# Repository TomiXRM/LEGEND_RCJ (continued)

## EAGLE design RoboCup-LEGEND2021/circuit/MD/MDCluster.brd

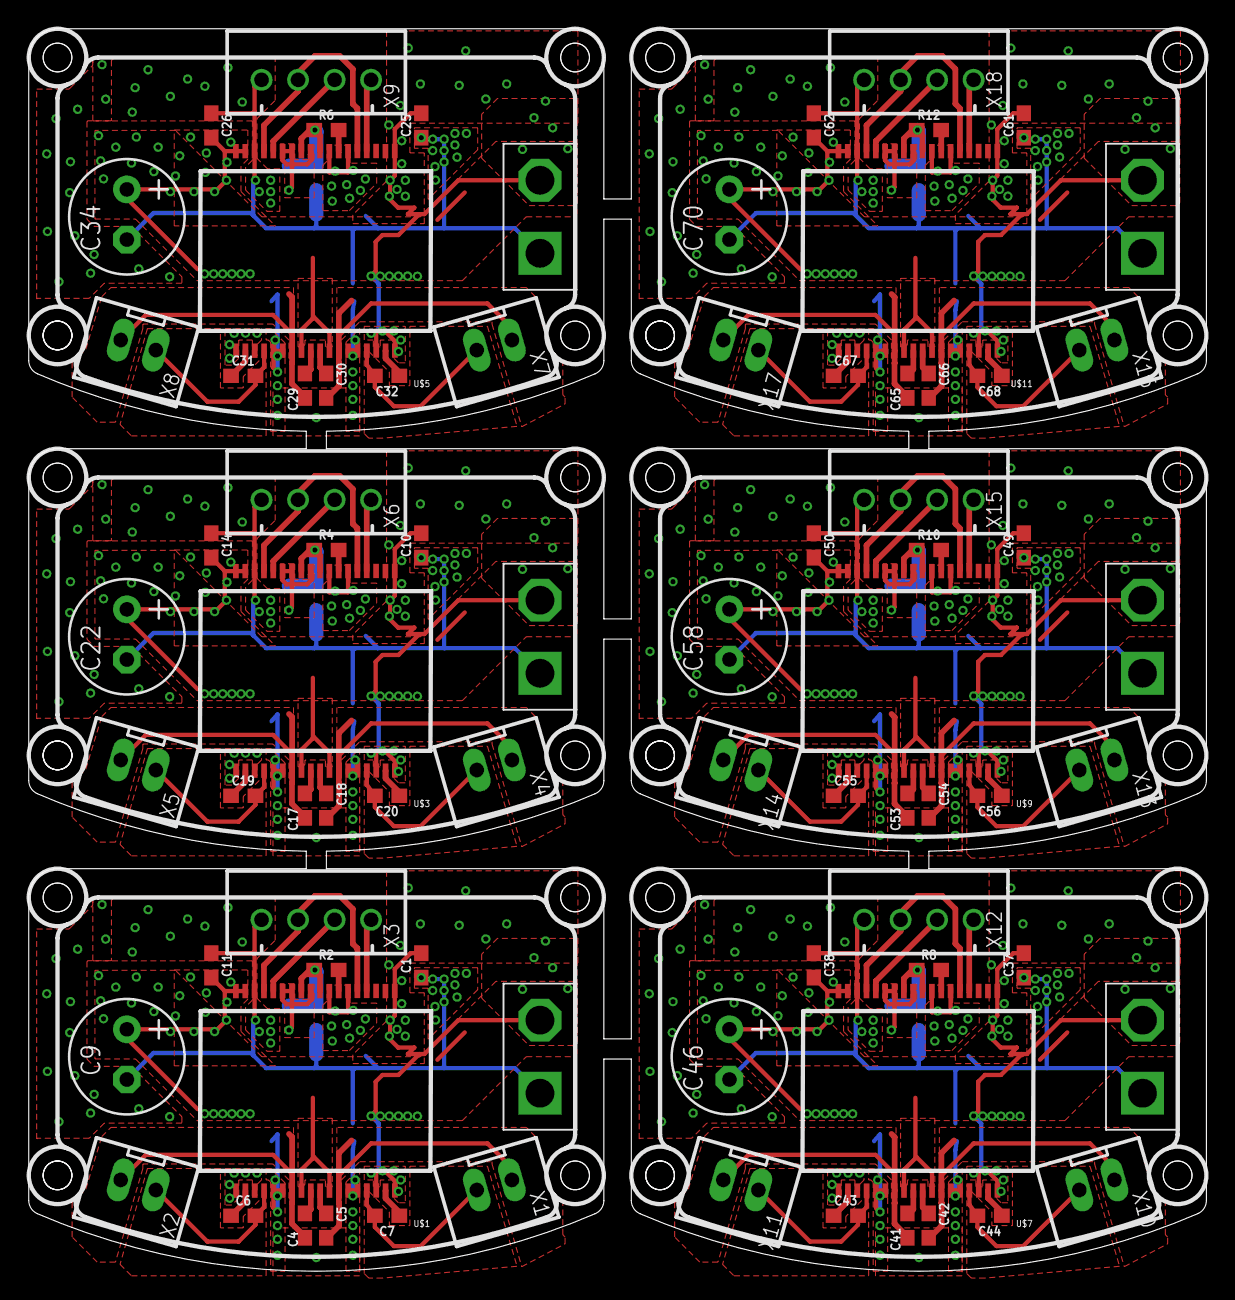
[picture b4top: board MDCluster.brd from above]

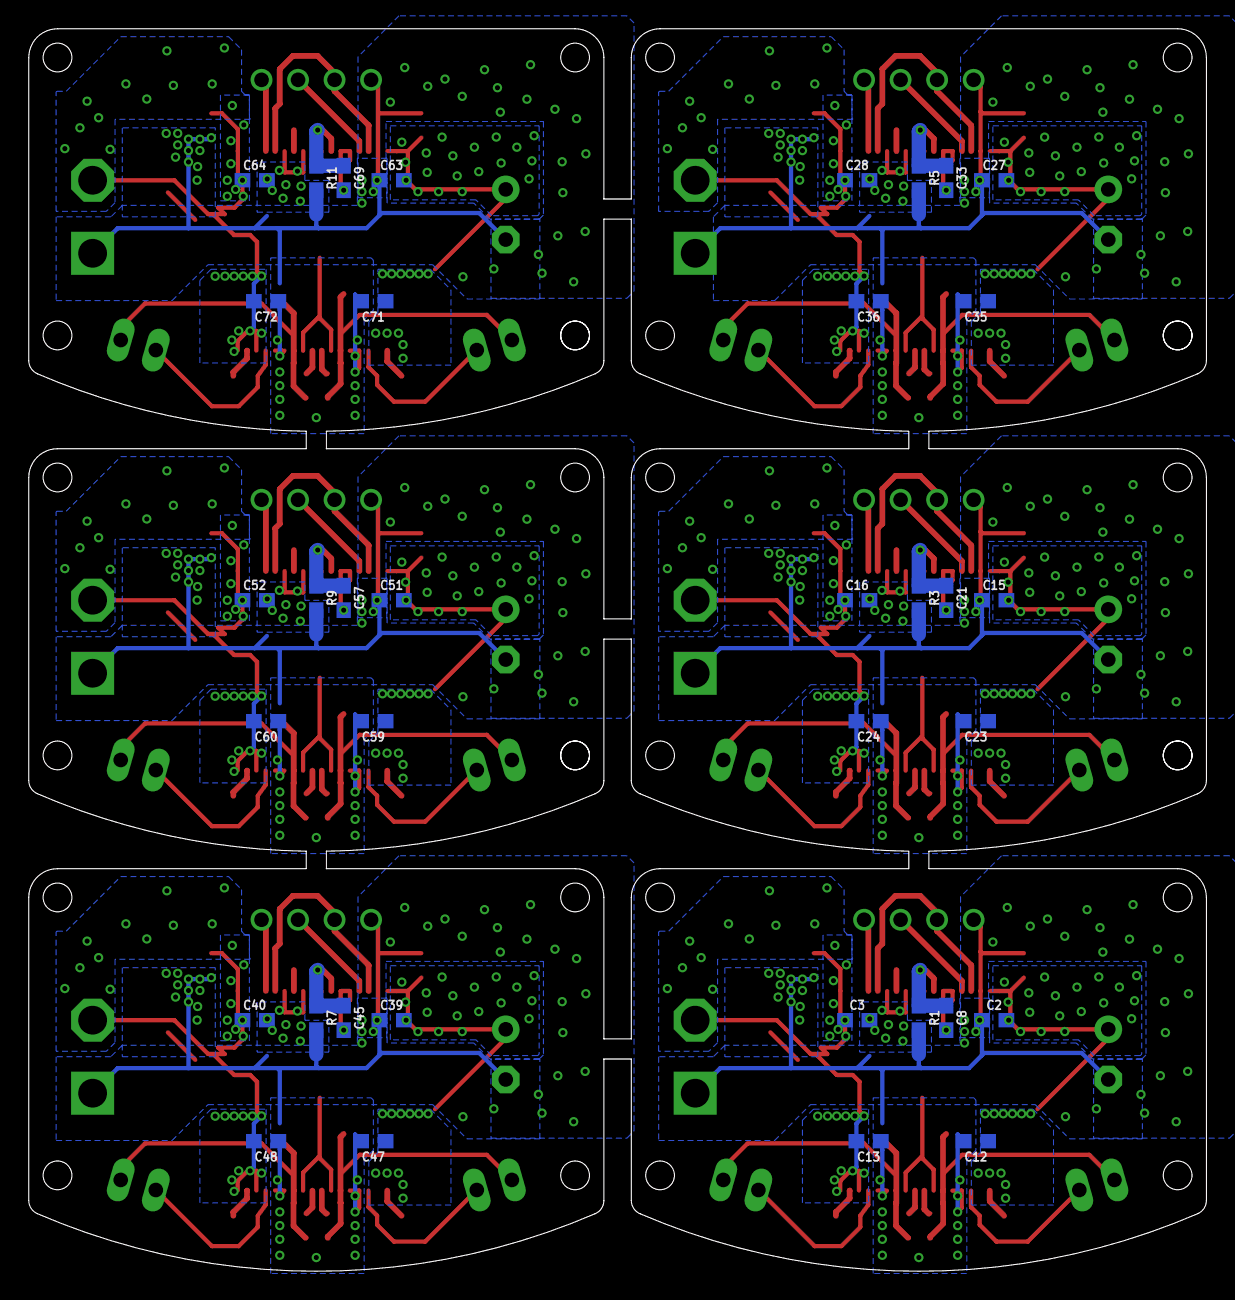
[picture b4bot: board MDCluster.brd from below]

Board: 2 copper layers, 81.9 x 86.4 mm, 114 parts (36 on the bottom side), 96 nets.

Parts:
C1, C2, C3, C4, C5, C6, C7, C8, C10, C11, C12, C13, C14, C15, C16, C17, C18, C19, C20, C21, C23, C24, C25, C26, C27, C28, C29, C30, C31, C32, C33, C35, C36, C37, C38, C39, C40, C41, C42, C43, C44, C45, C47, C48, C49, C50, C51, C52, C53, C54, C55, C56, C57, C59, C60, C61, C62, C63, C64, C65, C66, C67, C68, C69, C71, C72: 0.1uF; 0603
C9, C22, C34, C46, C58, C70: E3,5-8
R1, R3, R5, R7, R9, R11: 1; 0603
R2, R4, R6, R8, R10, R12: 47k; 0603
U$1, U$3, U$5, U$7, U$9, U$11: DRV8432DKDR; HSSOP-36
U$2, U$4, U$6, U$8, U$10, U$12: BAT
X1, X2, X4, X5, X7, X8, X10, X11, X13, X14, X16, X17: JST-XH-02-PIN-LONG-PAD; JST-XH-02-PACKAGE-LONG-PAD
X3, X6, X9, X12, X15, X18: JST-XH-04-PIN-ROUND-PAD; JST-XH-04-PACKAGE-ROUND-PAD

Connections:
AGND1: C8.1, R1.1, R2.1, U$1.AGND, U$1.M3
AGND2: C21.1, R3.1, R4.1, U$3.AGND, U$3.M3
AGND3: C33.1, R5.1, R6.1, U$5.AGND, U$5.M3
AGND4: C45.1, R7.1, R8.1, U$7.AGND, U$7.M3
AGND5: C57.1, R9.1, R10.1, U$9.AGND, U$9.M3
AGND6: C69.1, R11.1, R12.1, U$11.AGND, U$11.M3
GND: C1.1, C2.1, C3.2, C9.-, C11.1, C12.2, C13.1, R1.2, U$1.GND, U$1.GND_A, U$1.GND_B, U$1.GND_C, U$1.GND_D, U$1.PWM_B, U$1.PWM_D, U$2.G, X3.1
GND1: C10.1, C14.1, C15.1, C16.2, C22.-, C23.2, C24.1, R3.2, U$3.GND, U$3.GND_A, U$3.GND_B, U$3.GND_C, U$3.GND_D, U$3.PWM_B, U$3.PWM_D, U$4.G, X6.1
GND2: C25.1, C26.1, C27.1, C28.2, C34.-, C35.2, C36.1, R5.2, U$5.GND, U$5.GND_A, U$5.GND_B, U$5.GND_C, U$5.GND_D, U$5.PWM_B, U$5.PWM_D, U$6.G, X9.1
GND3: C37.1, C38.1, C39.1, C40.2, C46.-, C47.2, C48.1, R7.2, U$7.GND, U$7.GND_A, U$7.GND_B, U$7.GND_C, U$7.GND_D, U$7.PWM_B, U$7.PWM_D, U$8.G, X12.1
GND4: C49.1, C50.1, C51.1, C52.2, C58.-, C59.2, C60.1, R9.2, U$9.GND, U$9.GND_A, U$9.GND_B, U$9.GND_C, U$9.GND_D, U$9.PWM_B, U$9.PWM_D, U$10.G, X15.1
GND5: C61.1, C62.1, C63.1, C64.2, C70.-, C71.2, C72.1, R11.2, U$11.GND, U$11.GND_A, U$11.GND_B, U$11.GND_C, U$11.GND_D, U$11.PWM_B, U$11.PWM_D, U$12.G, X18.1
M1_1: C7.2, U$1.OUT_A, X1.2
M1_2: C5.2, U$1.OUT_B, X1.1
M1_3: C18.2, U$3.OUT_B, X4.1
M1_4: C20.2, U$3.OUT_A, X4.2
M1_5: C30.2, U$5.OUT_B, X7.1
M1_6: C32.2, U$5.OUT_A, X7.2
M1_7: C42.2, U$7.OUT_B, X10.1
M1_8: C44.2, U$7.OUT_A, X10.2
M1_9: C54.2, U$9.OUT_B, X13.1
M1_10: C56.2, U$9.OUT_A, X13.2
M1_11: C66.2, U$11.OUT_B, X16.1
M1_12: C68.2, U$11.OUT_A, X16.2
M2_1: C4.2, U$1.OUT_C, X2.2
M2_2: C6.2, U$1.OUT_D, X2.1
M2_3: C19.2, U$3.OUT_D, X5.1
M2_4: C17.2, U$3.OUT_C, X5.2
M2_5: C31.2, U$5.OUT_D, X8.1
M2_6: C29.2, U$5.OUT_C, X8.2
M2_7: C43.2, U$7.OUT_D, X11.1
M2_8: C41.2, U$7.OUT_C, X11.2
M2_9: C55.2, U$9.OUT_D, X14.1
M2_10: C53.2, U$9.OUT_C, X14.2
M2_11: C67.2, U$11.OUT_D, X17.1
M2_12: C65.2, U$11.OUT_C, X17.2
MDRST: U$1.RESET_AB, U$1.RESET_CD, X3.2
MDRST1: U$3.RESET_AB, U$3.RESET_CD, X6.2
MDRST2: U$5.RESET_AB, U$5.RESET_CD, X9.2
MDRST3: U$7.RESET_AB, U$7.RESET_CD, X12.2
MDRST4: U$9.RESET_AB, U$9.RESET_CD, X15.2
MDRST5: U$11.RESET_AB, U$11.RESET_CD, X18.2
unnamed: C19.1, U$3.BST_D
unnamed: C17.1, U$3.BST_C
unnamed: C18.1, U$3.BST_B
unnamed: C20.1, U$3.BST_A
unnamed: C6.1, U$1.BST_D
unnamed: C4.1, U$1.BST_C
unnamed: C5.1, U$1.BST_B
unnamed: C7.1, U$1.BST_A
unnamed: R4.2, U$3.OC_ADJ
unnamed: C31.1, U$5.BST_D
unnamed: C29.1, U$5.BST_C
unnamed: R2.2, U$1.OC_ADJ
unnamed: C30.1, U$5.BST_B
unnamed: C32.1, U$5.BST_A
unnamed: R6.2, U$5.OC_ADJ
unnamed: C43.1, U$7.BST_D
unnamed: C41.1, U$7.BST_C
unnamed: C42.1, U$7.BST_B
unnamed: C44.1, U$7.BST_A
unnamed: R8.2, U$7.OC_ADJ
unnamed: C55.1, U$9.BST_D
unnamed: C53.1, U$9.BST_C
unnamed: C54.1, U$9.BST_B
unnamed: C56.1, U$9.BST_A
unnamed: R10.2, U$9.OC_ADJ
unnamed: C67.1, U$11.BST_D
unnamed: C65.1, U$11.BST_C
unnamed: C66.1, U$11.BST_B
unnamed: C68.1, U$11.BST_A
unnamed: R12.2, U$11.OC_ADJ
PWM1: U$1.PWM_A, X3.4
PWM2: U$1.PWM_C, X3.3
PWM3: U$3.PWM_C, X6.3
PWM4: U$3.PWM_A, X6.4
PWM5: U$5.PWM_C, X9.3
PWM6: U$5.PWM_A, X9.4
PWM7: U$7.PWM_C, X12.3
PWM8: U$7.PWM_A, X12.4
PWM9: U$9.PWM_C, X15.3
PWM10: U$9.PWM_A, X15.4
PWM11: U$11.PWM_C, X18.3
PWM12: U$11.PWM_A, X18.4
VM: C1.2, C2.2, C3.1, C9.+, C11.2, C12.1, C13.2, U$1.GVDD_A, U$1.GVDD_B, U$1.GVDD_C, U$1.GVDD_D, U$1.PVDD_A, U$1.PVDD_B, U$1.PVDD_C, U$1.PVDD_D, U$1.VDD, U$2.+
VM1: C10.2, C14.2, C15.2, C16.1, C22.+, C23.1, C24.2, U$3.GVDD_A, U$3.GVDD_B, U$3.GVDD_C, U$3.GVDD_D, U$3.PVDD_A, U$3.PVDD_B, U$3.PVDD_C, U$3.PVDD_D, U$3.VDD, U$4.+
VM2: C25.2, C26.2, C27.2, C28.1, C34.+, C35.1, C36.2, U$5.GVDD_A, U$5.GVDD_B, U$5.GVDD_C, U$5.GVDD_D, U$5.PVDD_A, U$5.PVDD_B, U$5.PVDD_C, U$5.PVDD_D, U$5.VDD, U$6.+
VM3: C37.2, C38.2, C39.2, C40.1, C46.+, C47.1, C48.2, U$7.GVDD_A, U$7.GVDD_B, U$7.GVDD_C, U$7.GVDD_D, U$7.PVDD_A, U$7.PVDD_B, U$7.PVDD_C, U$7.PVDD_D, U$7.VDD, U$8.+
VM4: C49.2, C50.2, C51.2, C52.1, C58.+, C59.1, C60.2, U$9.GVDD_A, U$9.GVDD_B, U$9.GVDD_C, U$9.GVDD_D, U$9.PVDD_A, U$9.PVDD_B, U$9.PVDD_C, U$9.PVDD_D, U$9.VDD, U$10.+
VM5: C61.2, C62.2, C63.2, C64.1, C70.+, C71.1, C72.2, U$11.GVDD_A, U$11.GVDD_B, U$11.GVDD_C, U$11.GVDD_D, U$11.PVDD_A, U$11.PVDD_B, U$11.PVDD_C, U$11.PVDD_D, U$11.VDD, U$12.+
VREG1: C8.2, U$1.M1, U$1.M2, U$1.VREG
VREG2: C21.2, U$3.M1, U$3.M2, U$3.VREG
VREG3: C33.2, U$5.M1, U$5.M2, U$5.VREG
VREG4: C45.2, U$7.M1, U$7.M2, U$7.VREG
VREG5: C57.2, U$9.M1, U$9.M2, U$9.VREG
VREG6: C69.2, U$11.M1, U$11.M2, U$11.VREG

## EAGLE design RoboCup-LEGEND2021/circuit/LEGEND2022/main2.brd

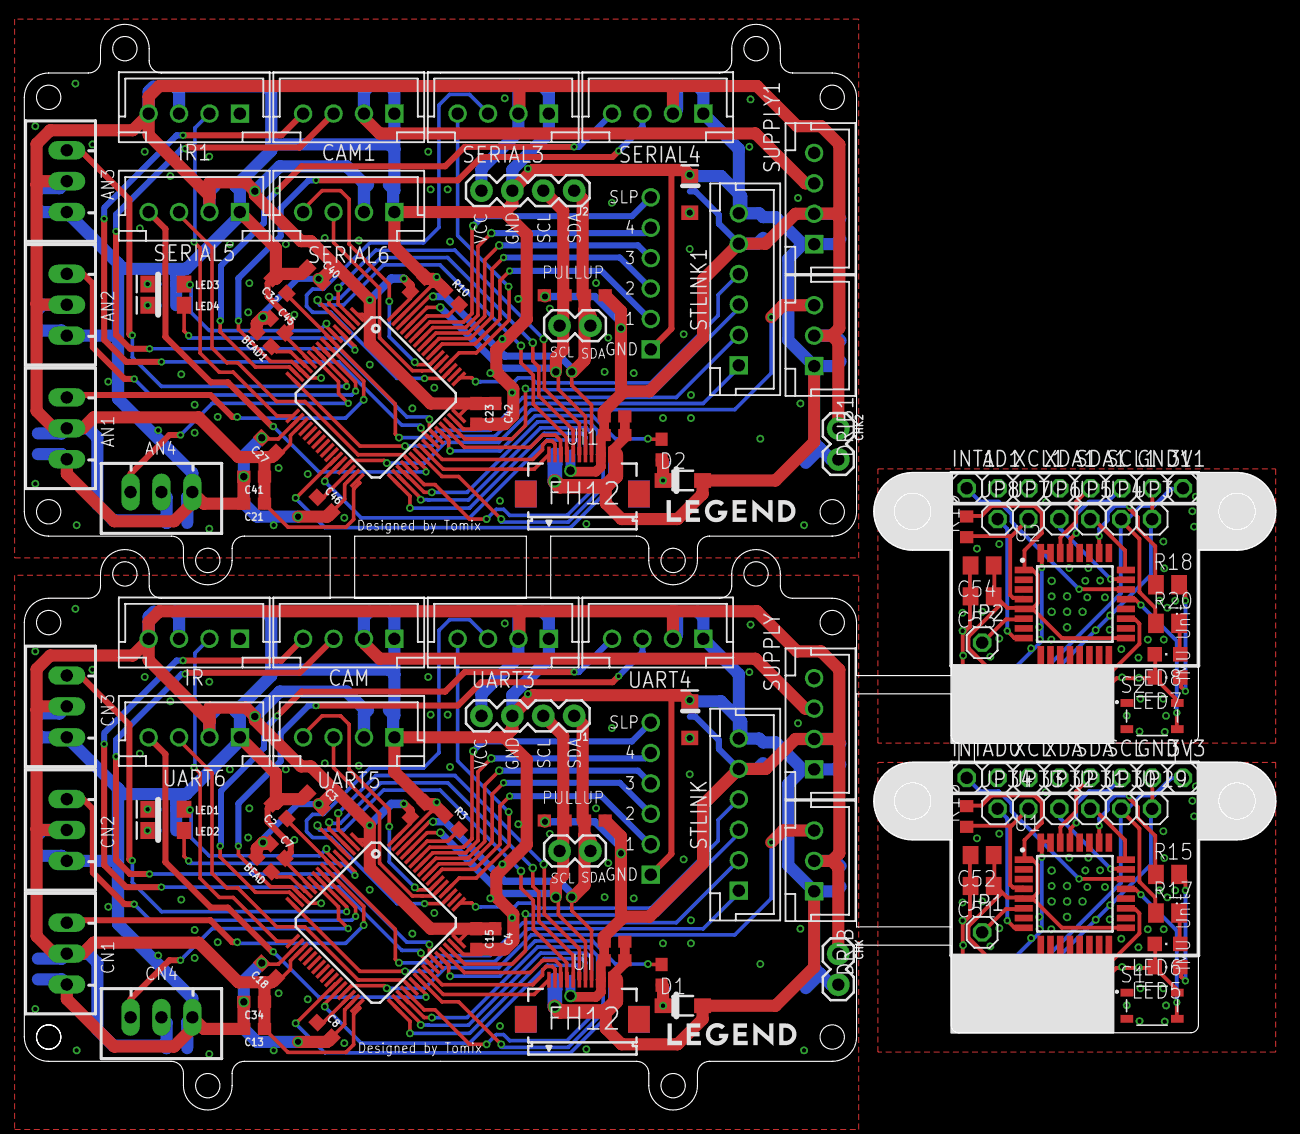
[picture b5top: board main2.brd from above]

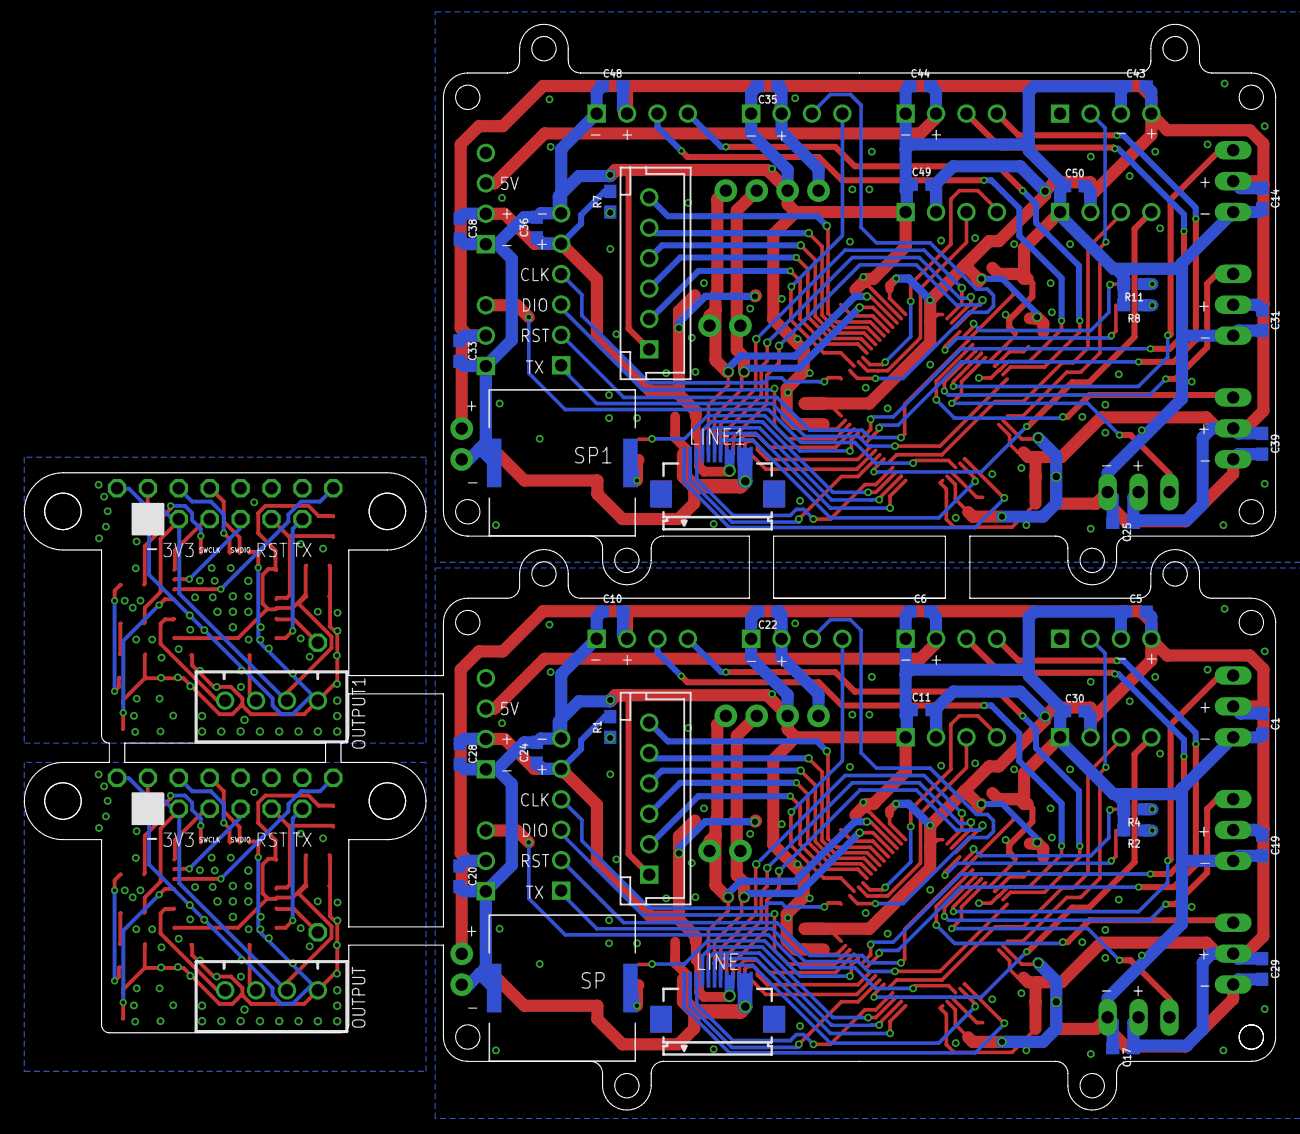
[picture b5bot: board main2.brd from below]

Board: 2 copper layers, 102.9 x 89.3 mm, 166 parts (40 on the bottom side), 136 nets.

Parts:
3V1, 3V3: 1X01
AD0, AD1: 1X01
AN1: 1; JST-XH-03-PACKAGE-LONG-PAD
AN2: 2; JST-XH-03-PACKAGE-LONG-PAD
AN3: 3; JST-XH-03-PACKAGE-LONG-PAD
AN4: 4; JST-XH-03-PACKAGE-LONG-PAD
BEAD, BEAD1: 0; 0603
C1, C14: 0.1uF; 1608
C2, C3, C4, C5, C6, C7, C10, C11, C12, C13, C15, C16, C17, C18, C19, C20, C21, C22, C23, C24, C25, C27, C30, C31, C32, C33, C35, C36, C40, C42, C43, C44, C45, C48, C49, C50: 0.1UF_1608; 1608
C8, C46: 4.7uF; 0603
C9, C34, C41, C47: 0.1uF; 0603
C26, C37: 0.001UF_1608; 1608
C28, C29, C38, C39: 1.0UF_1608; 1608
C51, C52, C53, C54: 0.1u; C0805
CAM, CAM1: cam; B4B-XH-A
CHK, CHK1, CHK2, CHK3: +3V3; 1X02
CN1: 1; JST-XH-03-PACKAGE-LONG-PAD
CN2: 2; JST-XH-03-PACKAGE-LONG-PAD
CN3: 3; JST-XH-03-PACKAGE-LONG-PAD
CN4: 4; JST-XH-03-PACKAGE-LONG-PAD
D1, D2: DIODE-SS2040LFL; SOD123FL
DRIB, DRIB1: B3B-XH-A
GND, GND1: 1X01
INT, INT1: 1X01
IR, IR1: IR; B4B-XH-A
J1, J2: 1X04
JP1, JP2, JP3, JP4, JP5, JP6, JP7, JP8, JP29, JP30, JP31, JP32, JP33, JP34: 1X01
LED1, LED2, LED3, LED4: LED-1206
LED5, LED6, LED7, LED8: CHIPLED_0805
LINE, LINE1: FH12-12S-0.5SH
MD_A, MD_A1: B6B-XH-A
NUCLEO_MAIN, NUCLEO_MAIN1: F446RET6; STM32F446RET6
OUTPUT, OUTPUT1: JST-XH-04-PIN-ROUND-PAD; JST-XH-04-PACKAGE-ROUND-PAD
PILOT, PILOT1: LED-1206
R1, R2, R4, R5, R6, R7, R8, R9, R11, R12, R13, R14: 1k; R0603
R3, R10, R16, R19: 10k; R0603
R15, R17, R18, R20: 1k; M0805
S1, S2: SKRPACE010; SW_SKRPACE010
SCL, SCL1: 1X01
SDA, SDA1: 1X01
SERIAL3, SERIAL4, SERIAL5, SERIAL6: IMU; B4B-XH-A
SP, SP1: PKLCS1212E4001
STLINK, STLINK1: MAIN; B6B-XH-A
SUPPLY, SUPPLY1: B4B-XH-A
U1, U2: STM32F303K8T6; QFP80P900X900X160-32N
UART3, UART4, UART5, UART6: IMU; B4B-XH-A
UI, UI1: FH12-12S-0.5SH
XCL, XCL1: 1X01
XDA, XDA1: 1X01

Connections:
+3V1: 3V1.1, C53.1, C54.1, JP4.1, OUTPUT1.2, R19.2, R20.1, U2.1, U2.5, U2.17
+3V3: 3V3.1, C51.1, C52.1, JP30.1, OUTPUT.2, R16.2, R17.1, U1.1, U1.5, U1.17
+5V: C6.2, CAM.2, SUPPLY.3
+5V1: C44.2, CAM1.2, SUPPLY1.3
A0: JP1.1, U1.6
A9: JP2.1, U2.6
ANALOG: OUTPUT.3, U1.10
ANALOG1: OUTPUT1.3, U2.10
BALLRX: IR.2, NUCLEO_MAIN.PA3
BALLRX1: IR1.2, NUCLEO_MAIN1.PA3
BOOT0: NUCLEO_MAIN.BOOT0, R3.2
BOOT1: NUCLEO_MAIN1.BOOT0, R10.2
BUTTON_CENTER: NUCLEO_MAIN.PC14, UI.5
BUTTON_CENTER1: NUCLEO_MAIN1.PC14, UI1.5
BUTTON_LEFT: NUCLEO_MAIN.PC15, UI.4
BUTTON_LEFT1: NUCLEO_MAIN1.PC15, UI1.4
BUTTON_RIGHT: NUCLEO_MAIN.PC13, UI.6
BUTTON_RIGHT1: NUCLEO_MAIN1.PC13, UI1.6
BUZZER: NUCLEO_MAIN.PA11, R9.1
BUZZER1: NUCLEO_MAIN1.PA11, R12.1
CN1: CN1.3, NUCLEO_MAIN.PC0
CN2: CN2.3, NUCLEO_MAIN.PC1
CN3: CN3.3, NUCLEO_MAIN.PC2
CN4: CN4.3, NUCLEO_MAIN.PC3
CN5: AN1.3, NUCLEO_MAIN1.PC0
CN6: AN2.3, NUCLEO_MAIN1.PC1
CN7: AN3.3, NUCLEO_MAIN1.PC2
CN8: AN4.3, NUCLEO_MAIN1.PC3
D5: R18.1, U2.26
D13: R15.1, U1.26
DRIB_PWM: DRIB.3, NUCLEO_MAIN.PB10
DRIB_PWM1: DRIB1.3, NUCLEO_MAIN1.PB10
GND: C51.2, C52.2, GND.1, JP29.1, LED5.C, LED6.C, OUTPUT.1, S1.2, U1.16, U1.31, U1.32
GND1: C53.2, C54.2, GND1.1, JP3.1, LED7.C, LED8.C, OUTPUT1.1, S2.2, U2.16, U2.31, U2.32
INT: INT.1, U1.22
INT1: INT1.1, U2.22
LED1: LED1.A, NUCLEO_MAIN.PH1
LED2: LED2.A, NUCLEO_MAIN.PH0
LED3: LED4.A, NUCLEO_MAIN1.PH0
LED4: LED3.A, NUCLEO_MAIN1.PH1
LINE_A0: LINE.6, NUCLEO_MAIN.PB12
LINE_A1: LINE.5, NUCLEO_MAIN.PB13
LINE_A2: LINE.4, NUCLEO_MAIN.PB14
LINE_A3: LINE.3, NUCLEO_MAIN.PB15
LINE_A4: LINE.2, NUCLEO_MAIN.PC8
LINE_A5: LINE1.2, NUCLEO_MAIN1.PC8
LINE_A6: LINE1.3, NUCLEO_MAIN1.PB15
LINE_A7: LINE1.4, NUCLEO_MAIN1.PB14
LINE_A8: LINE1.5, NUCLEO_MAIN1.PB13
LINE_A9: LINE1.6, NUCLEO_MAIN1.PB12
LINE_ANALOG: LINE.1, NUCLEO_MAIN.PB1
LINE_ANALOG1: LINE1.1, NUCLEO_MAIN1.PB1
LINE_PWM: LINE.7, NUCLEO_MAIN.PB2
LINE_PWM1: LINE1.7, NUCLEO_MAIN1.PB2
unnamed: LED2.C, R2.1
unnamed: LED1.C, R4.1
unnamed: LED4.C, R8.1
unnamed: LED3.C, R11.1
unnamed: LED5.A, R15.2
unnamed: LED6.A, R17.2
unnamed: LED7.A, R18.2
unnamed: LED8.A, R20.2
NRST: C2.1, NUCLEO_MAIN.NRST, STLINK.2
NRST1: C32.1, NUCLEO_MAIN1.NRST, STLINK1.2
PH1: MD_A.2, NUCLEO_MAIN.PB3
PH2: MD_A.3, NUCLEO_MAIN.PB4
PH3: MD_A.4, NUCLEO_MAIN.PB5
PH4: MD_A.5, NUCLEO_MAIN.PB6
PH5: MD_A1.4, NUCLEO_MAIN1.PB5
PH6: MD_A1.3, NUCLEO_MAIN1.PB4
PH7: MD_A1.2, NUCLEO_MAIN1.PB3
PH8: MD_A1.5, NUCLEO_MAIN1.PB6
POWERLED_RESISTOR: PILOT.A, R1.1
POWERLED_RESISTOR1: PILOT1.A, R7.1
RESET: JP33.1, R16.1, U1.4
RESET1: JP7.1, R19.1, U2.4
RGB_B: NUCLEO_MAIN.PA12, UI.3
RGB_B1: NUCLEO_MAIN1.PA12, UI1.3
RGB_G: NUCLEO_MAIN.PA8, UI.2
RGB_G1: NUCLEO_MAIN1.PA8, UI1.2
RGB_R: NUCLEO_MAIN.PC9, UI.1
RGB_R1: NUCLEO_MAIN1.PC9, UI1.1
SCL: CHK1.1, J1.2, NUCLEO_MAIN.PB8, R6.1, UI.7
SCL1: CHK3.1, J2.2, NUCLEO_MAIN1.PB8, R14.1, UI1.7
SCL2: SCL.1, U1.29
SCL3: SCL1.1, U2.29
SDA: CHK1.2, J1.1, NUCLEO_MAIN.PB9, R5.1, UI.8
SDA1: CHK3.2, J2.1, NUCLEO_MAIN1.PB9, R13.1, UI1.8
SDA2: SDA.1, U1.30
SDA3: SDA1.1, U2.30
SERIAL1RX: CAM.3, NUCLEO_MAIN.PA10
SERIAL1RX1: CAM1.3, NUCLEO_MAIN1.PA10
SERIAL1TX: CAM.4, NUCLEO_MAIN.PA9
SERIAL1TX1: CAM1.4, NUCLEO_MAIN1.PA9
SERIAL3RX: NUCLEO_MAIN.PC11, UART3.4
SERIAL3RX1: NUCLEO_MAIN1.PC11, SERIAL3.4
SERIAL3TX: NUCLEO_MAIN.PC10, UART3.3
SERIAL3TX1: NUCLEO_MAIN1.PC10, SERIAL3.3
SERIAL4RX: NUCLEO_MAIN.PA1, UART4.4
SERIAL4RX1: NUCLEO_MAIN1.PA1, SERIAL4.4
SERIAL4TX: NUCLEO_MAIN.PA0, UART4.3
SERIAL4TX1: NUCLEO_MAIN1.PA0, SERIAL4.3
SERIAL5RX: NUCLEO_MAIN.PD2, UART5.4
SERIAL5RX1: NUCLEO_MAIN1.PD2, SERIAL6.4
SERIAL5TX: NUCLEO_MAIN.PC12, UART5.3
SERIAL5TX1: NUCLEO_MAIN1.PC12, SERIAL6.3
SERIAL6RX: NUCLEO_MAIN.PC7, UART6.4
SERIAL6RX1: NUCLEO_MAIN1.PC7, SERIAL5.4
SERIAL6TX: NUCLEO_MAIN.PC6, UART6.3
SERIAL6TX1: NUCLEO_MAIN1.PC6, SERIAL5.3
SLEEP: MD_A.6, NUCLEO_MAIN.PB7
SLEEP1: MD_A1.6, NUCLEO_MAIN1.PB7
SP: D1.C, R9.2, SP.1
SP1: D2.C, R12.2, SP1.1
SW: S1.4, U1.21
SW1: S2.4, U2.21
SWCLK: NUCLEO_MAIN.PA14, STLINK.4
SWCLK1: NUCLEO_MAIN1.PA14, STLINK1.4
SWCLK2: JP31.1, U1.24
SWCLK3: JP5.1, U2.24
SWDIO: NUCLEO_MAIN.PA13, STLINK.3
SWDIO1: NUCLEO_MAIN1.PA13, STLINK1.3
SWDIO2: JP32.1, U1.23
SWDIO3: JP6.1, U2.23
TX1: OUTPUT.4, U1.19
TX2: OUTPUT1.4, U2.19
USBTX: NUCLEO_MAIN.PA2, STLINK.1
USBTX1: NUCLEO_MAIN1.PA2, STLINK1.1
USBTX2: JP34.1, U1.8
USBTX3: JP8.1, U2.8
VCAP: C8.1, NUCLEO_MAIN.VCAP_1
VCAP1: C46.1, NUCLEO_MAIN1.VCAP_1
VCC: AN1.2, AN2.2, AN3.2, AN4.2, BEAD.2, BEAD1.2, C1.1, C3.2, C4.1, C5.2, C7.1, C9.1, C10.2, C11.2, C12.1, C13.1, C14.1, C15.1, C16.1, C17.1, C18.1, C19.1, C20.1, C21.1, C22.1, C23.1, C24.1, C25.1, C26.1, C27.1, C28.1, C29.1, C30.2, C31.1, C33.1, C34.1, C35.1, C36.1, C37.1, C38.1, C39.1, C40.2, C41.1, C42.1, C43.2, C45.1, C47.1, C48.2, C49.2, C50.2, CHK.1, CHK2.1, CN1.2, CN2.2, CN3.2, CN4.2, DRIB.2, DRIB1.2, IR.4, IR1.4, J1.4, J2.4, LINE.8, LINE.9, LINE1.8, LINE1.9, NUCLEO_MAIN.VBAT, NUCLEO_MAIN.VDD, NUCLEO_MAIN.VDD1, NUCLEO_MAIN.VDD2, NUCLEO_MAIN.VDD3, NUCLEO_MAIN1.VBAT, NUCLEO_MAIN1.VDD, NUCLEO_MAIN1.VDD1, NUCLEO_MAIN1.VDD2, NUCLEO_MAIN1.VDD3, R1.2, R5.2, R6.2, R7.2, R13.2, R14.2, SERIAL3.2, SERIAL4.2, SERIAL5.2, SERIAL6.2, STLINK.5, STLINK1.5, SUPPLY.2, SUPPLY1.2, UART3.2, UART4.2, UART5.2, UART6.2, UI.9, UI.10, UI1.9, UI1.10
VDDA: BEAD.1, NUCLEO_MAIN.VREF+
VDDA1: BEAD1.1, NUCLEO_MAIN1.VREF+
VSS: AN1.1, AN2.1, AN3.1, AN4.1, C1.2, C2.2, C3.1, C4.2, C5.1, C6.1, C7.2, C8.2, C9.2, C10.1, C11.1, C12.2, C13.2, C14.2, C15.2, C16.2, C17.2, C18.2, C19.2, C20.2, C21.2, C22.2, C23.2, C24.2, C25.2, C26.2, C27.2, C28.2, C29.2, C30.1, C31.2, C32.2, C33.2, C34.2, C35.2, C36.2, C37.2, C38.2, C39.2, C40.1, C41.2, C42.2, C43.1, C44.1, C45.2, C46.2, C47.2, C48.1, C49.1, C50.1, CAM.1, CAM1.1, CHK.2, CHK2.2, CN1.1, CN2.1, CN3.1, CN4.1, D1.A, D2.A, DRIB.1, DRIB1.1, IR.3, IR1.3, J1.3, J2.3, LINE.10, LINE.11, LINE.12, LINE1.10, LINE1.11, LINE1.12, MD_A.1, MD_A1.1, NUCLEO_MAIN.VREF-, NUCLEO_MAIN.VSS, NUCLEO_MAIN.VSS1, NUCLEO_MAIN.VSS2, NUCLEO_MAIN.VSS3, NUCLEO_MAIN1.VREF-, NUCLEO_MAIN1.VSS, NUCLEO_MAIN1.VSS1, NUCLEO_MAIN1.VSS2, NUCLEO_MAIN1.VSS3, PILOT.C, PILOT1.C, R2.2, R3.1, R4.2, R8.2, R10.1, R11.2, SERIAL3.1, SERIAL4.1, SERIAL5.1, SERIAL6.1, SP.2, SP1.2, STLINK.6, STLINK1.6, SUPPLY.1, SUPPLY1.1, UART3.1, UART4.1, UART5.1, UART6.1, UI.11, UI.12, UI1.11, UI1.12

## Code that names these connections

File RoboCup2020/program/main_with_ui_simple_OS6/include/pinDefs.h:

#pragma once
//LED
#define LED1 PB_8
#define LED2 PB_9
#define LED3 PF_13

//LINE Sensor
#define LINE_SIG PA_0
#define LINE_A0 PG_2
#define LINE_A1 PG_3
#define LINE_A2 PG_4
#define LINE_A3 PG_5
#define LINE_A4 PG_6
#define LINE_PWM PD_15

//Button
#define BUTTON_LEFT PD_7
#define BUTTON_CENTRE PG_9
#define BUTTON_RIGHT PG_10

//Buzzer
#define BUZZER PC_6

//Dribbler
#define DRIB_PWM PE_5

//Kicker
#define KICKER_PHOTO1 PA_2
#define KICKER_PHOTO2 PA_3
#define KICKER_KICK PF_2

//EEPROM
#define EEPROM_SDA PF_0
#define EEPROM_SCL PF_1

//INA219
#define INA219_SDA PC_9
#define INA219_SCL PA_8

//OLED
#define LCD_SDA PB_7
#define LCD_SCL PB_6

//I2C (FREE)
#define I2C_SDA PF_15
#define I2C_SCL PF_14

//CN (ADC)
#define CN1 PF_3
#define CN2 PF_4
#define CN3 PF_5
#define CN4 PF_6
#define CN5 PF_7
#define CN6 PF_8
#define CN7 PF_9
#define CN8 PF_10
#define CN9 PC_0
#define CN10 PC_1
#define CN11 PC_2

//Bridge
#define BRIDGE_TX PA_9
#define BRIDGE_RX PA_10
#define BRIDGE_IO1 PA_4
#define BRIDGE_IO2 PA_5

//UART
#define UART_A_TX PG_14
#define UART_A_RX PC_7

#define UART_B_TX PE_8
#define UART_B_RX PE_7

#define UART_C_TX PE_1
#define UART_C_RX PE_0

//IMU
#define IMU_TX PC_10
#define IMU_RX PC_11

//MOUSE
#define MOUSE_TX PC_12
#define MOUSE_RX PD_2

//CAM
#define CAM_TX PD_5
#define CAM_RX PD_6

//PC&IR
#define PC_TX PD_8
#define IR_RX PD_9
#define IR_INT PE_15

//RGB
#define RGB_R PD_14
#define RGB_G PD_13
#define RGB_B PD_12

//DIPSW
#define DIPSW1 PF_11
#define DIPSW2 PF_12
#define DIPSW3 PG_0
#define DIPSW4 PG_1

//Motor
#define MD_SLP PE_10
//[A]
#define MD_A_EN1 PA_1
#define MD_A_PH1 PE_9
#define MD_A_EN2 PE_11
#define MD_A_PH2 PA_15

//[B]
#define MD_B_EN1 PE_13
#define MD_B_PH1 PE_14
#define MD_B_EN2 PB_10
#define MD_B_PH2 PB_11

//SPI
#define SPI_SCK PB_3
#define SPI_MISO PB_4
#define SPI_MOSI PB_5

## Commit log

2023-12-11 add all files
2023-12-11 remove cut2d
2023-12-11 remove main
2023-12-11 add main
2024-01-07 🍣京滋奈ブロック2024でmbedOSをアップデートした物を追加

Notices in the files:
parts and their libraries:
SparkFun-Resistors: Licensing: Creative Commons ShareAlike 4.0 International - https://creativecommons.org/licenses/by-sa/4.0
cap-pan40: Copyright (C) 2004, Bob Starr
